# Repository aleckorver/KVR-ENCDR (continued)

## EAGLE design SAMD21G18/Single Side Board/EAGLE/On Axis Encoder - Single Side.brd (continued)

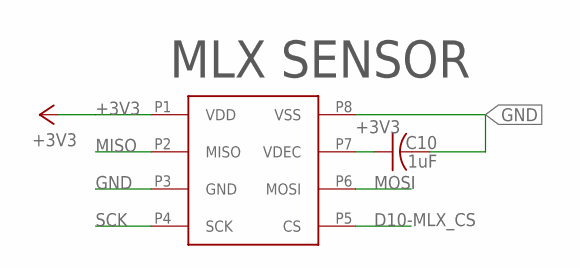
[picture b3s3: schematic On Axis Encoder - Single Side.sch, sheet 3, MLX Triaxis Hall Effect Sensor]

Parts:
C10: 1uF; C0603
U$4: MLX90363-SOIC8; SOIC-8

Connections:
+3V3: C10.1, U$4.P1 (VDD), U$4.P7 (VDEC); also elsewhere on the board
D10-MLX_CS: U$4.P5 (CS); also elsewhere on the board
GND: C10.2, U$4.P3 (GND), U$4.P8 (VSS); also elsewhere on the board
MISO: U$4.P2 (MISO); also elsewhere on the board
MOSI: U$4.P6 (MOSI); also elsewhere on the board
SCK: U$4.P4 (SCK); also elsewhere on the board

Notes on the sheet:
MLX SENSOR

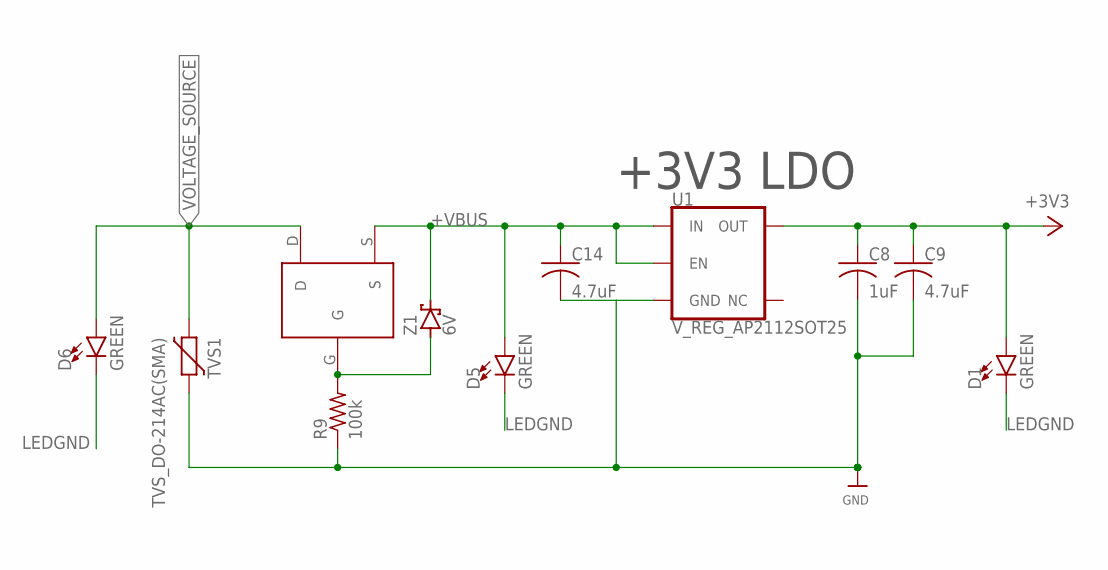
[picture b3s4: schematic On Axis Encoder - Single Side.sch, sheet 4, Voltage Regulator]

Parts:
C8: 1uF; C0603
C9, C14: 4.7uF; C0603
D1, D5, D6: GREEN; LED-0603
PFET1: PFET; SOT323-3_NFET
R9: 100k; R0603
TVS1: TVS_DO-214AC(SMA); DIOM5226X290N
U1: V_REG_AP2112SOT25; SOT95P285X140-5N
Z1: 6V; SOT23

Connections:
+3V3: C8.1, C9.1, D1.A, U1.5 (OUT); also elsewhere on the board
+VBUS: C14.1, D5.A, PFET1.S, U1.1 (IN), U1.3 (EN), Z1.3 (C); also elsewhere on the board
GND: C8.2, C9.2, C14.2, R9.1, TVS1.2, U1.2 (GND); also elsewhere on the board
LEDGND: D1.C, D5.C, D6.C; also elsewhere on the board
unnamed: PFET1.G, R9.2, Z1.1 (A)
VOLTAGE_SOURCE: D6.A, PFET1.D, TVS1.1; also elsewhere on the board

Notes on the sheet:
+3V3 LDO

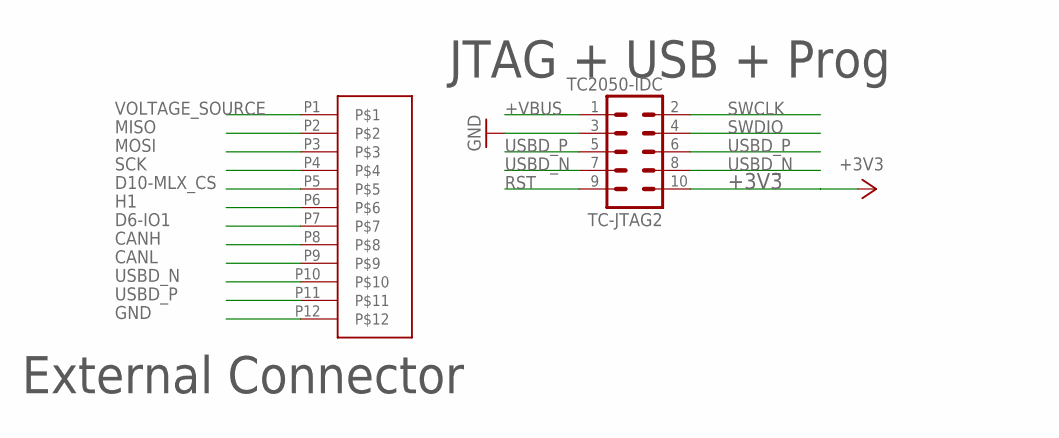
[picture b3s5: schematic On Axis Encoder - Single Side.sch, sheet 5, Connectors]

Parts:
TC-JTAG2: TC2050-IDC
U$9: BM12B-ZESS-TBT; JST-BM12B-ZESS-TBT

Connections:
+3V3: TC-JTAG2.10; also elsewhere on the board
+VBUS: TC-JTAG2.1; also elsewhere on the board
CANH: U$9.P8; also elsewhere on the board
CANL: U$9.P9; also elsewhere on the board
D6-IO1: U$9.P7; also elsewhere on the board
D10-MLX_CS: U$9.P5; also elsewhere on the board
GND: TC-JTAG2.3, U$9.P12; also elsewhere on the board
H1: U$9.P6; also elsewhere on the board
MISO: U$9.P2; also elsewhere on the board
MOSI: U$9.P3; also elsewhere on the board
RST: TC-JTAG2.9; also elsewhere on the board
SCK: U$9.P4; also elsewhere on the board
SWCLK: TC-JTAG2.2; also elsewhere on the board
SWDIO: TC-JTAG2.4; also elsewhere on the board
USBD_N: TC-JTAG2.7, TC-JTAG2.8, U$9.P10; also elsewhere on the board
USBD_P: TC-JTAG2.5, TC-JTAG2.6, U$9.P11; also elsewhere on the board
VOLTAGE_SOURCE: U$9.P1; also elsewhere on the board

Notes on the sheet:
JTAG + USB + Prog
External Connector

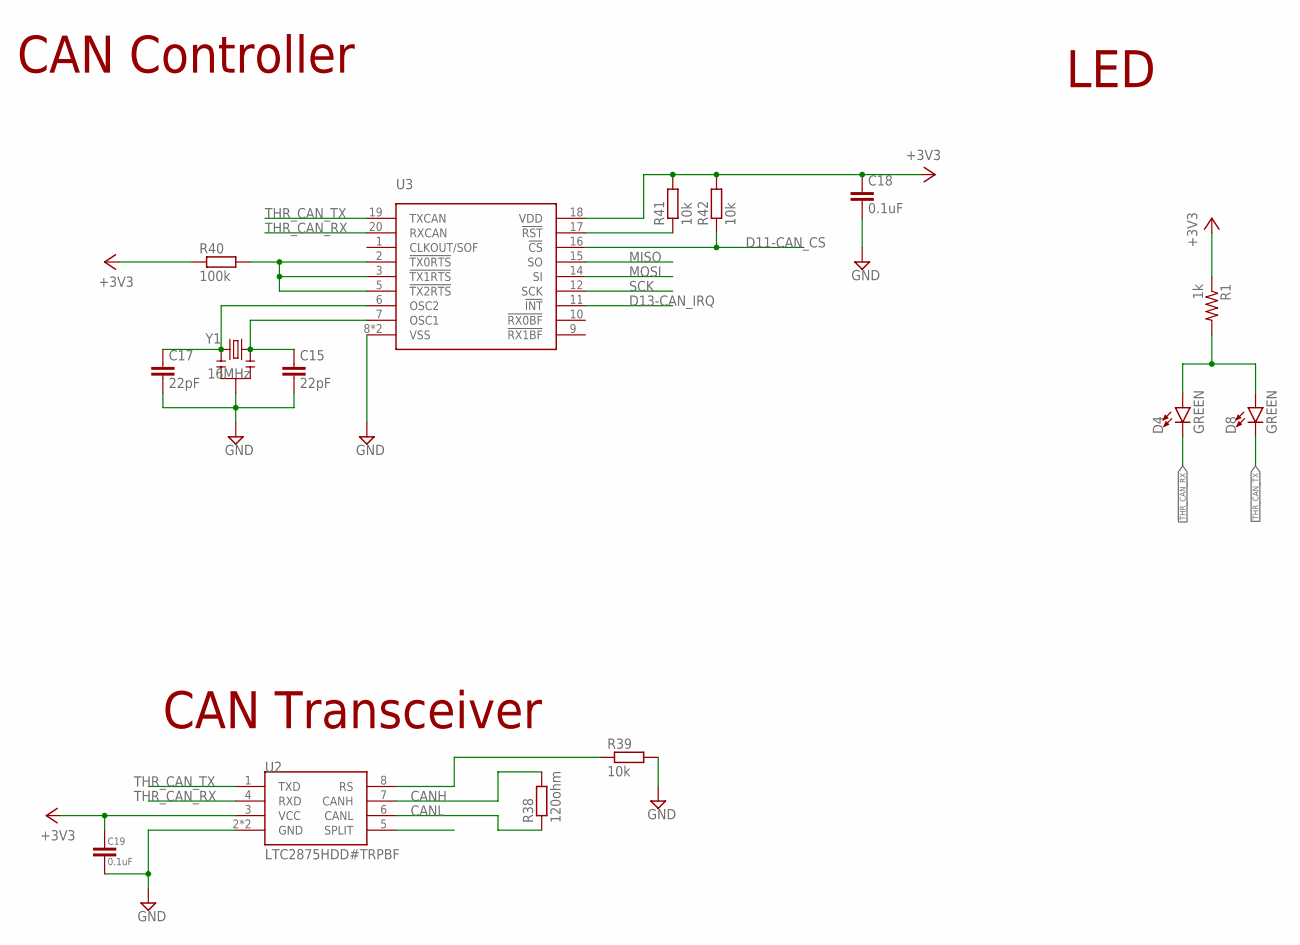
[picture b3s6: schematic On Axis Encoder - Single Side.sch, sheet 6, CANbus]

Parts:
C15, C17: 22pF; C-0603
C18, C19: 0.1uF; C-0603
D4, D8: GREEN; LED-0603
R1: 1k; R0603
R38: 120ohm; R-0603
R39, R41, R42: 10k; R-0603
R40: 100k; R-0603
U2: LTC2875HDD#TRPBF; SON50P300X300X80-9T165X238N
U3: MCP2515-E/ML; QFN50P400X400X100-21T270N
Y1: 16MHz; RESONATOR-SMD

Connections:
+3V3: C18.P$1 (1), C19.P$1 (1), R1.1, R40.P$1 (1), R41.P$2 (2), R42.P$2 (2), U2.3 (VCC), U3.18 (VDD); also elsewhere on the board
CANH: R38.P$2 (2), U2.7 (CANH); also elsewhere on the board
CANL: R38.P$1 (1), U2.6 (CANL); also elsewhere on the board
D11-CAN_CS: R42.P$1 (1), U3.16 (!CS); also elsewhere on the board
D13-CAN_IRQ: U3.11 (!INT); also elsewhere on the board
GND: C15.P$2 (2), C17.P$2 (2), C18.P$2 (2), C19.P$2 (2), R39.P$2 (2), U2.2 (GND), U2.9 (GND), U3.8 (VSS), U3.21 (VSS), Y1.2; also elsewhere on the board
MISO: U3.15 (SO); also elsewhere on the board
MOSI: U3.14 (SI); also elsewhere on the board
unnamed: D4.A, D8.A, R1.2
unnamed: R39.P$1 (1), U2.8 (RS)
unnamed: R41.P$1 (1), U3.17 (!RST)
unnamed: R40.P$2 (2), U3.2 (!TX0RTS), U3.3 (!TX1RTS), U3.5 (!TX2RTS)
unnamed: C17.P$1 (1), U3.6 (OSC2), Y1.3
unnamed: C15.P$1 (1), U3.7 (OSC1), Y1.1
SCK: U3.12 (SCK); also elsewhere on the board
THR_CAN_RX: D4.C, U2.4 (RXD), U3.20 (RXCAN)
THR_CAN_TX: D8.C, U2.1 (TXD), U3.19 (TXCAN)

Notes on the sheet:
CAN Transceiver
CAN Controller
LED

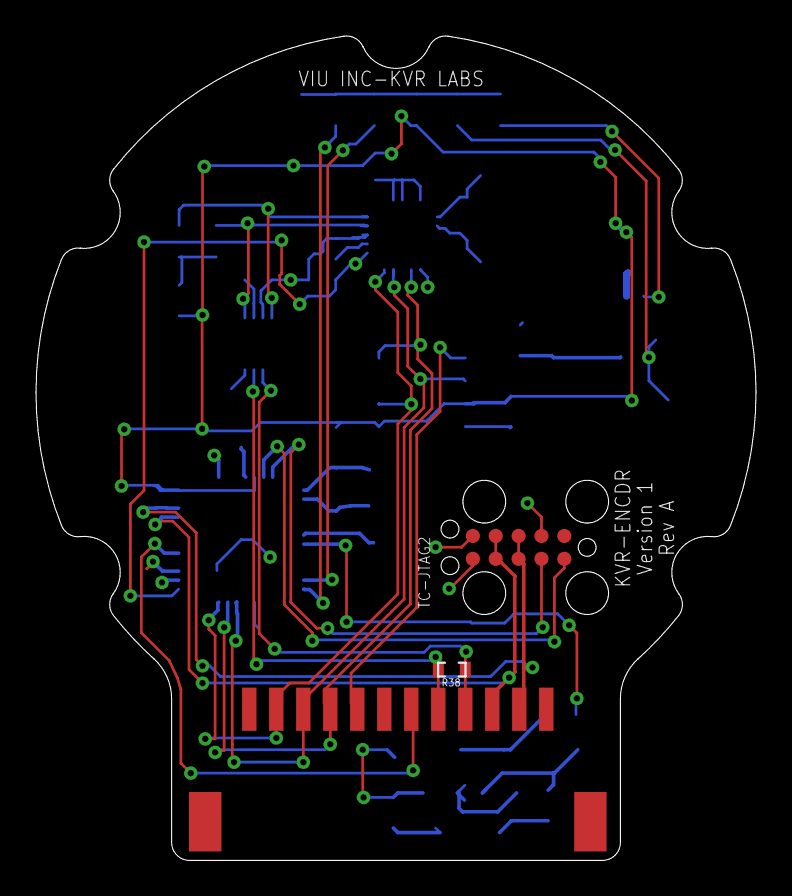
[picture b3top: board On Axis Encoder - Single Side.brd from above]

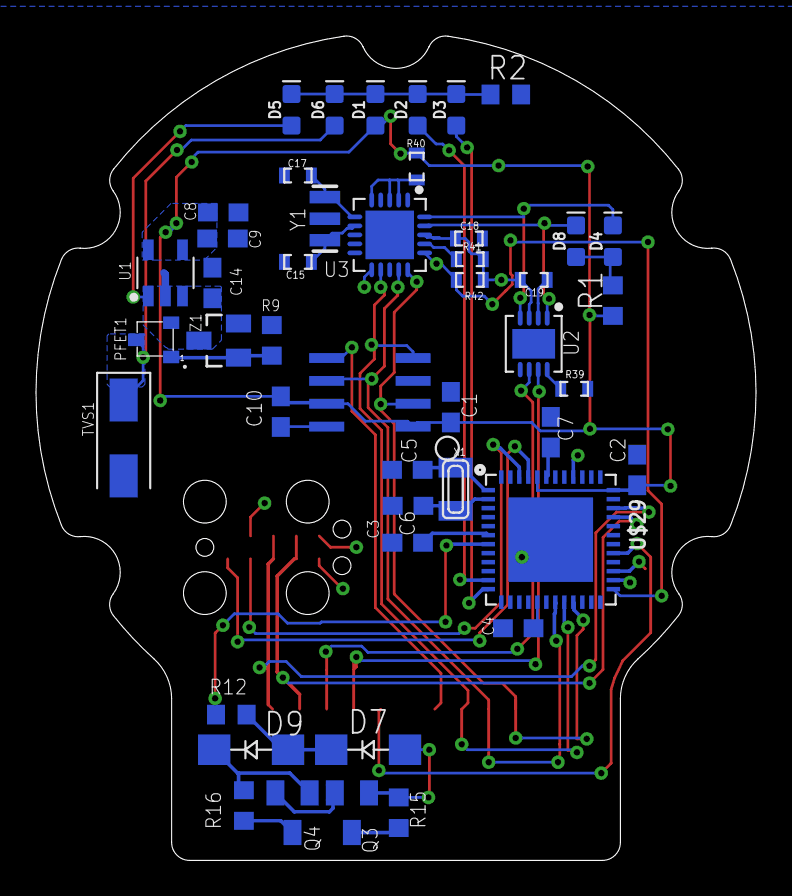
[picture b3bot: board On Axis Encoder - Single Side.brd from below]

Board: 4 copper layers, 40.0 x 45.8 mm, 49 parts (46 on the bottom side), 39 nets.

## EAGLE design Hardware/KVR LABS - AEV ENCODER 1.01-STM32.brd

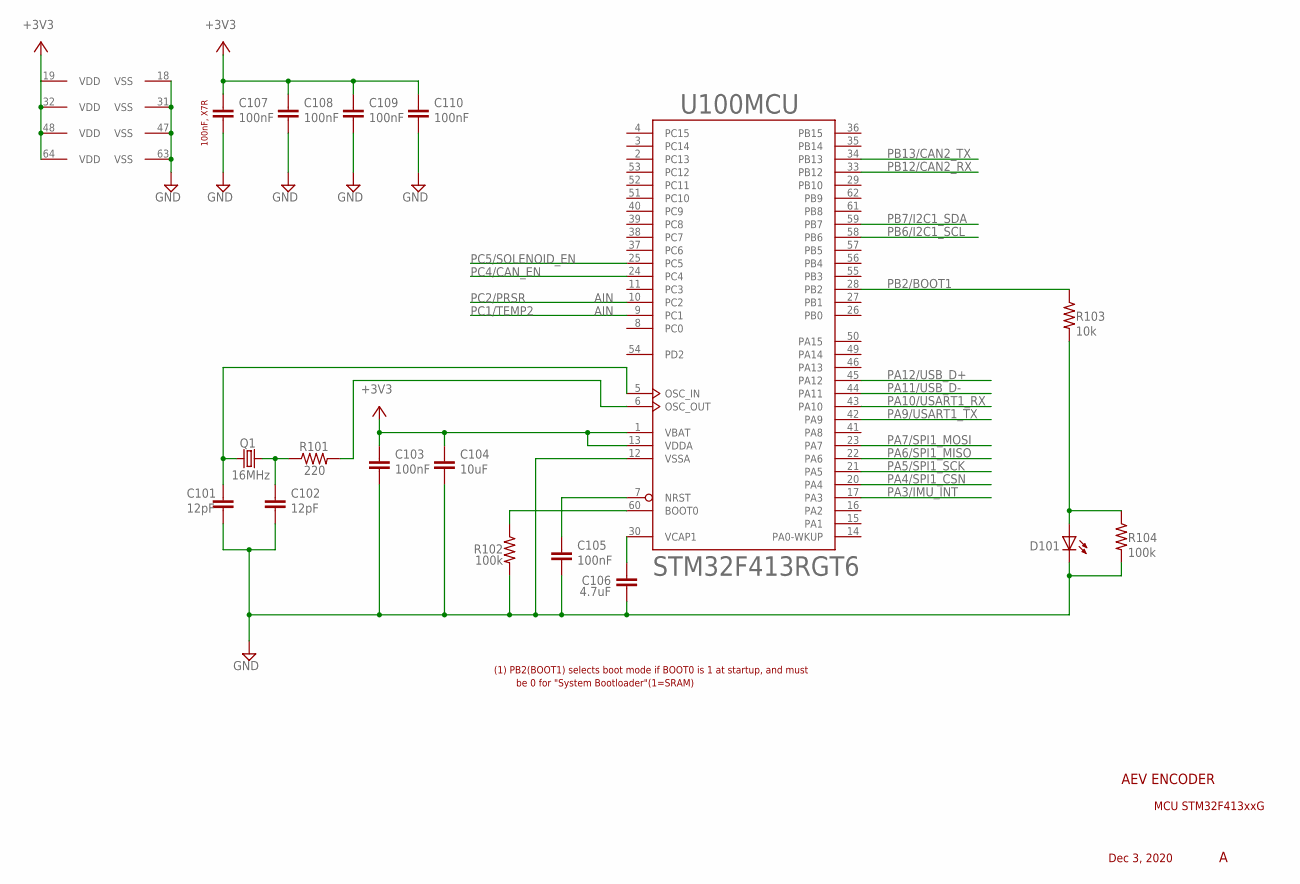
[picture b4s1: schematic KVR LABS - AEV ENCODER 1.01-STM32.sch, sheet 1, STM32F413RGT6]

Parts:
C101, C102: 12pF; C0603
C103, C105, C107, C108, C109, C110: 100nF; C0603
C104: 10uF; C0603
C106: 4.7uF; C0603
D101: LEDCHIPLED_0805; CHIPLED_0805
Q1: 16MHz; CRY3225-4
R101: 220; R0603
R102, R104: 100k; R0603
R103: 10k; R0603
U100: STM32F413RGT6; LQFP64_STMLIB

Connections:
+3V3: C103.1, C104.1, C107.1, C108.1, C109.1, C110.1, U100.1 (VBAT), U100.13 (VDDA), U100.19 (VDD), U100.32 (VDD), U100.48 (VDD), U100.64 (VDD); also elsewhere on the board
BOOT0: R102.1, U100.60 (BOOT0); also elsewhere on the board
GND: C101.2, C102.2, C103.2, C104.2, C105.2, C106.2, C107.2, C108.2, C109.2, C110.2, D101.C, R102.2, R104.2, U100.12 (VSSA), U100.18 (VSS), U100.31 (VSS), U100.47 (VSS), U100.63 (VSS); also elsewhere on the board
unnamed: D101.A, R103.2, R104.1
unnamed: R101.2, U100.6 (OSC_OUT)
NRST: C105.1, U100.7 (NRST)
OSC_IN: C101.1, Q1.3 (2), U100.5 (OSC_IN)
OSC_OUT: C102.1, Q1.1, R101.1
PA3/IMU_INT: U100.17 (PA3); also elsewhere on the board
PA4/SPI1_CSN: U100.20 (PA4); also elsewhere on the board
PA5/SPI1_SCK: U100.21 (PA5); also elsewhere on the board
PA6/SPI1_MISO: U100.22 (PA6); also elsewhere on the board
PA7/SPI1_MOSI: U100.23 (PA7); also elsewhere on the board
PA9/USART1_TX: U100.42 (PA9); also elsewhere on the board
PA10/USART1_RX: U100.43 (PA10); also elsewhere on the board
PA11/USB_D-: U100.44 (PA11); also elsewhere on the board
PA12/USB_D+: U100.45 (PA12); also elsewhere on the board
PB2/BOOT1: R103.1, U100.28 (PB2); also elsewhere on the board
PB6/I2C1_SCL: U100.58 (PB6); also elsewhere on the board
PB7/I2C1_SDA: U100.59 (PB7); also elsewhere on the board
PB12/CAN2_RX: U100.33 (PB12); also elsewhere on the board
PB13/CAN2_TX: U100.34 (PB13); also elsewhere on the board
PC1/TEMP2: U100.9 (PC1); also elsewhere on the board
PC2/PRSR: U100.10 (PC2); also elsewhere on the board
PC4/CAN_EN: U100.24 (PC4); also elsewhere on the board
PC5/SOLENOID_EN: U100.25 (PC5); also elsewhere on the board
VCAP: C106.1, U100.30 (VCAP1)

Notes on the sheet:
AEV ENCODER
MCU STM32F413xxG
Dec 3, 2020
100nF, X7R
(1) PB2(BOOT1) selects boot mode if BOOT0 is 1 at startup, and must
be 0 for "System Bootloader"(1=SRAM)
AIN

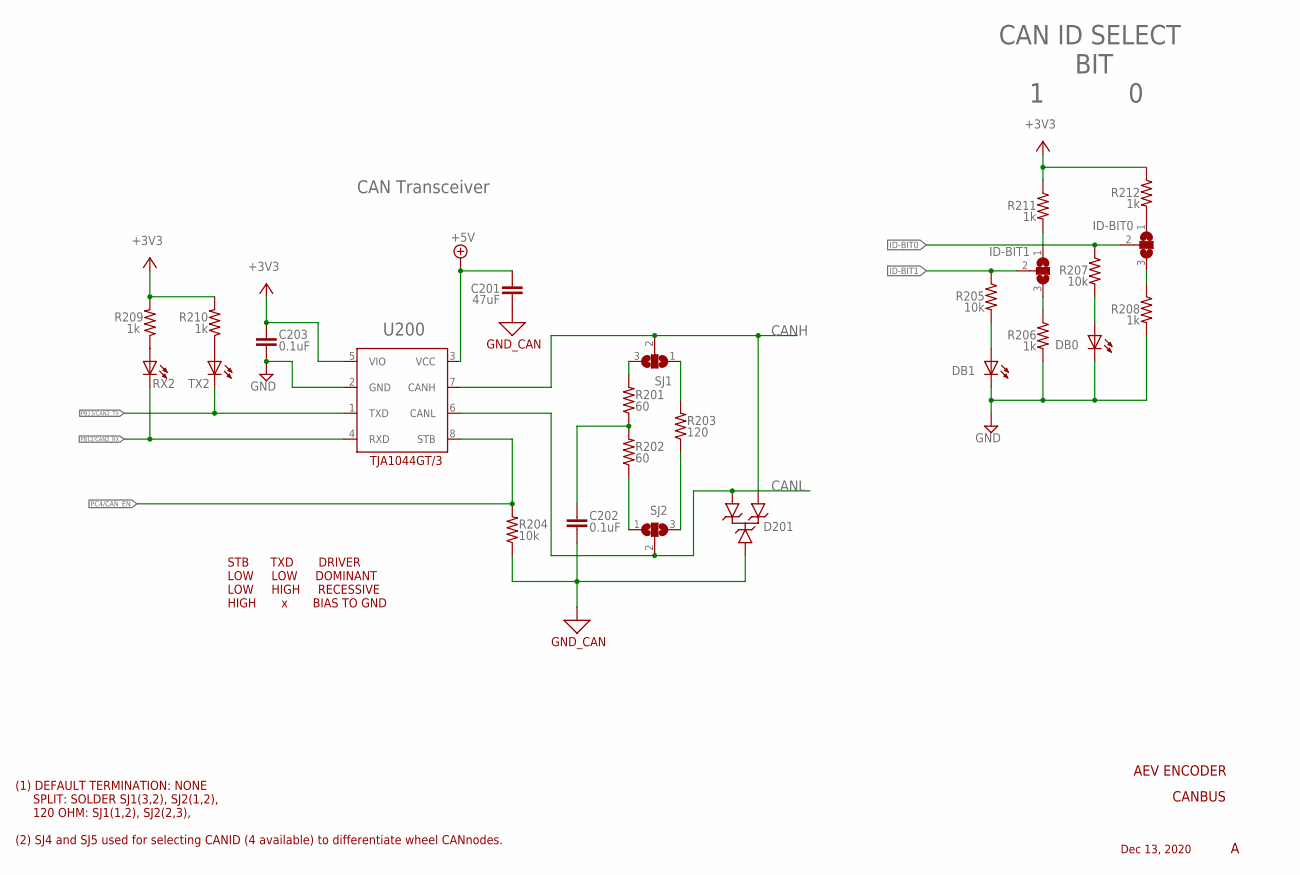
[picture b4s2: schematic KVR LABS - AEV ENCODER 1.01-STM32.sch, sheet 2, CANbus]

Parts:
C201: 47uF; C0603
C202, C203: 0.1uF; C0603
D201: μCLAMP2492SQ; SOT-23_3L_ONS
DB0, DB1: LEDCHIPLED_0805; CHIPLED_0805
ID-BIT0, ID-BIT1: SJ2W; SJ_2
R201, R202: 60; R0603
R203: 120; R0603
R204, R205, R207: 10k; R0603
R206, R208, R209, R210, R211, R212: 1k; R0603
RX2: LEDCHIPLED_0805; CHIPLED_0805
SJ1, SJ2: SJ2W; SJ_2
TX2: LEDCHIPLED_0805; CHIPLED_0805
U200: TJA1044GT/3; SO-8_S_LIT

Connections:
+3V3: C203.1, R209.2, R210.2, R211.1, R212.1, U200.5 (VIO); also elsewhere on the board
+5V: C201.1, U200.3 (VCC); also elsewhere on the board
CANH: D201.2, SJ1.2, U200.7 (CANH); also elsewhere on the board
CANL: D201.1, SJ2.2, U200.6 (CANL); also elsewhere on the board
GND: C203.2, DB0.C, DB1.C, R206.2, R208.2, U200.2 (GND); also elsewhere on the board
GND_CAN: C201.2, C202.2, D201.3, R204.1; also elsewhere on the board
ID-BIT0: ID-BIT0.2, R207.1
ID-BIT1: ID-BIT1.2, R205.1
unnamed: ID-BIT1.3, R206.1
unnamed: ID-BIT0.3, R208.1
unnamed: DB0.A, R207.2
unnamed: DB1.A, R205.2
unnamed: ID-BIT1.1, R211.2
unnamed: ID-BIT0.1, R212.2
unnamed: R209.1, RX2.A
unnamed: R210.1, TX2.A
PB12/CAN2_RX: RX2.C, U200.4 (RXD); also elsewhere on the board
PB13/CAN2_TX: TX2.C, U200.1 (TXD); also elsewhere on the board
PC4/CAN_EN: R204.2, U200.8 (STB); also elsewhere on the board
RSH: R201.2, SJ1.3
RSL: R202.1, SJ2.1
RTH: R203.2, SJ1.1
RTL: R203.1, SJ2.3
SPLIT: C202.1, R201.1, R202.2

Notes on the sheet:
CANBUS
AEV ENCODER
Dec 13, 2020
(1) DEFAULT TERMINATION: NONE SPLIT: SOLDER SJ1(3,2), SJ2(1,2), 120 OHM: SJ1(1,2), SJ2(2,3), (2) SJ4 and SJ5 used for selecting CANID (4 available) to differentiate wheel CANnodes.
CAN ID SELECT BIT 1 0
D201
CAN Transceiver
U200
STB TXD DRIVER LOW LOW DOMINANT LOW HIGH RECESSIVE HIGH x BIAS TO GND

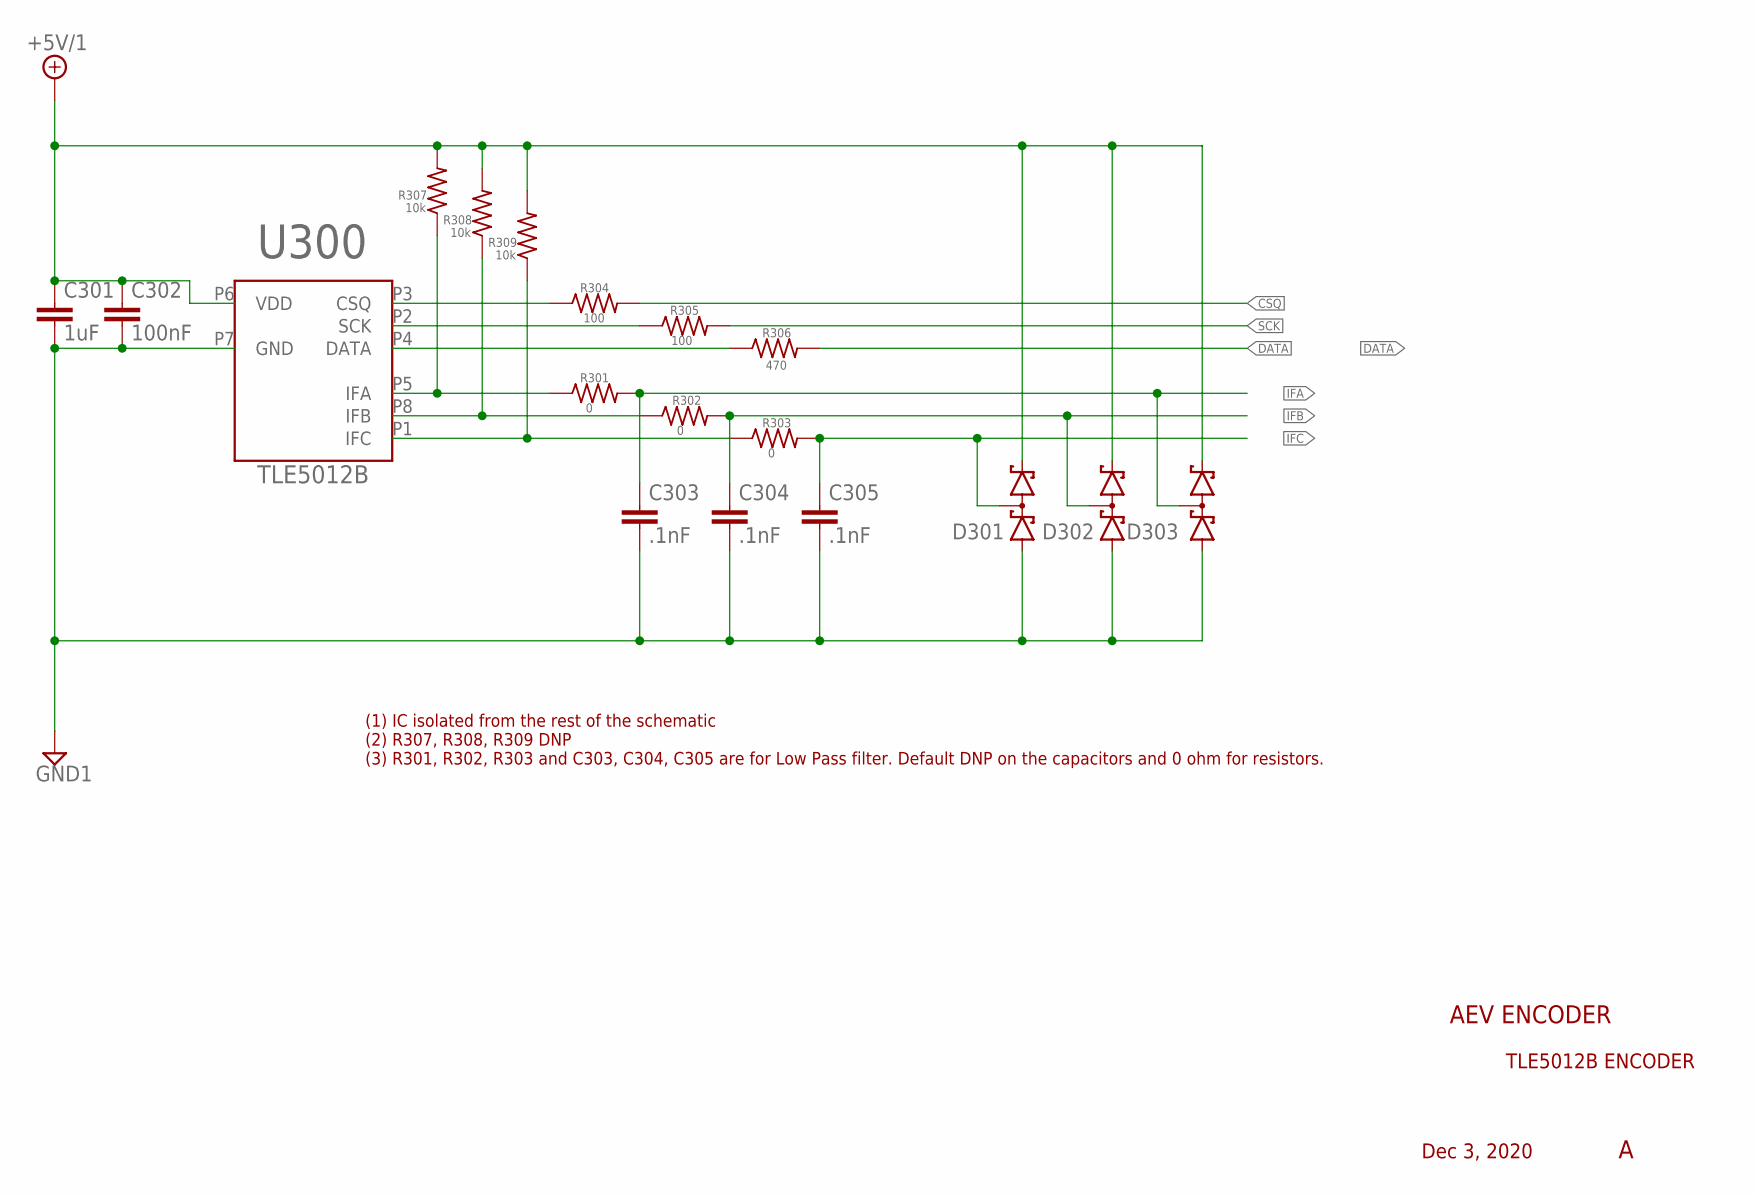
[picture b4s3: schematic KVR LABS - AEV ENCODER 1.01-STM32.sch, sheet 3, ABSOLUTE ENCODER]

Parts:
C301: 1uF; C0603
C302: 100nF; C0603
C303, C304, C305: .1nF; C0603
D301, D302, D303: BAS70-04; SOT23
R301, R302, R303: 0; R0603
R304, R305: 100; R0603
R306: 470; R0603
R307, R308, R309: 10k; R0603
U300: TLE5012B; PG-DSO-8

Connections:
+5V/1: C301.1, C302.1, D301.2 (C2), D302.2 (C2), D303.2 (C2), R307.2, R308.2, R309.2, U300.P6 (VDD); also elsewhere on the board
CSQ: R304.2; also elsewhere on the board
DATA: R306.2; also elsewhere on the board
GND1: C301.2, C302.2, C303.2, C304.2, C305.2, D301.1 (A1), D302.1 (A1), D303.1 (A1), U300.P7 (GND); also elsewhere on the board
IFA: C303.1, D303.3 (C1A2), R301.2; also elsewhere on the board
IFB: C304.1, D302.3 (C1A2), R302.2; also elsewhere on the board
IFC: C305.1, D301.3 (C1A2), R303.2; also elsewhere on the board
unnamed: R304.1, U300.P3 (CSQ)
unnamed: R305.1, U300.P2 (SCK)
unnamed: R306.1, U300.P4 (DATA)
unnamed: R301.1, R307.1, U300.P5 (IFA)
unnamed: R302.1, R308.1, U300.P8 (IFB)
unnamed: R303.1, R309.1, U300.P1 (IFC)
SCK: R305.2; also elsewhere on the board

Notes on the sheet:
TLE5012B
AEV ENCODER
TLE5012B ENCODER
Dec 3, 2020
U300
(1) IC isolated from the rest of the schematic (2) R307, R308, R309 DNP (3) R301, R302, R303 and C303, C304, C305 are for Low Pass filter. Default DNP on the capacitors and 0 ohm for resistors.

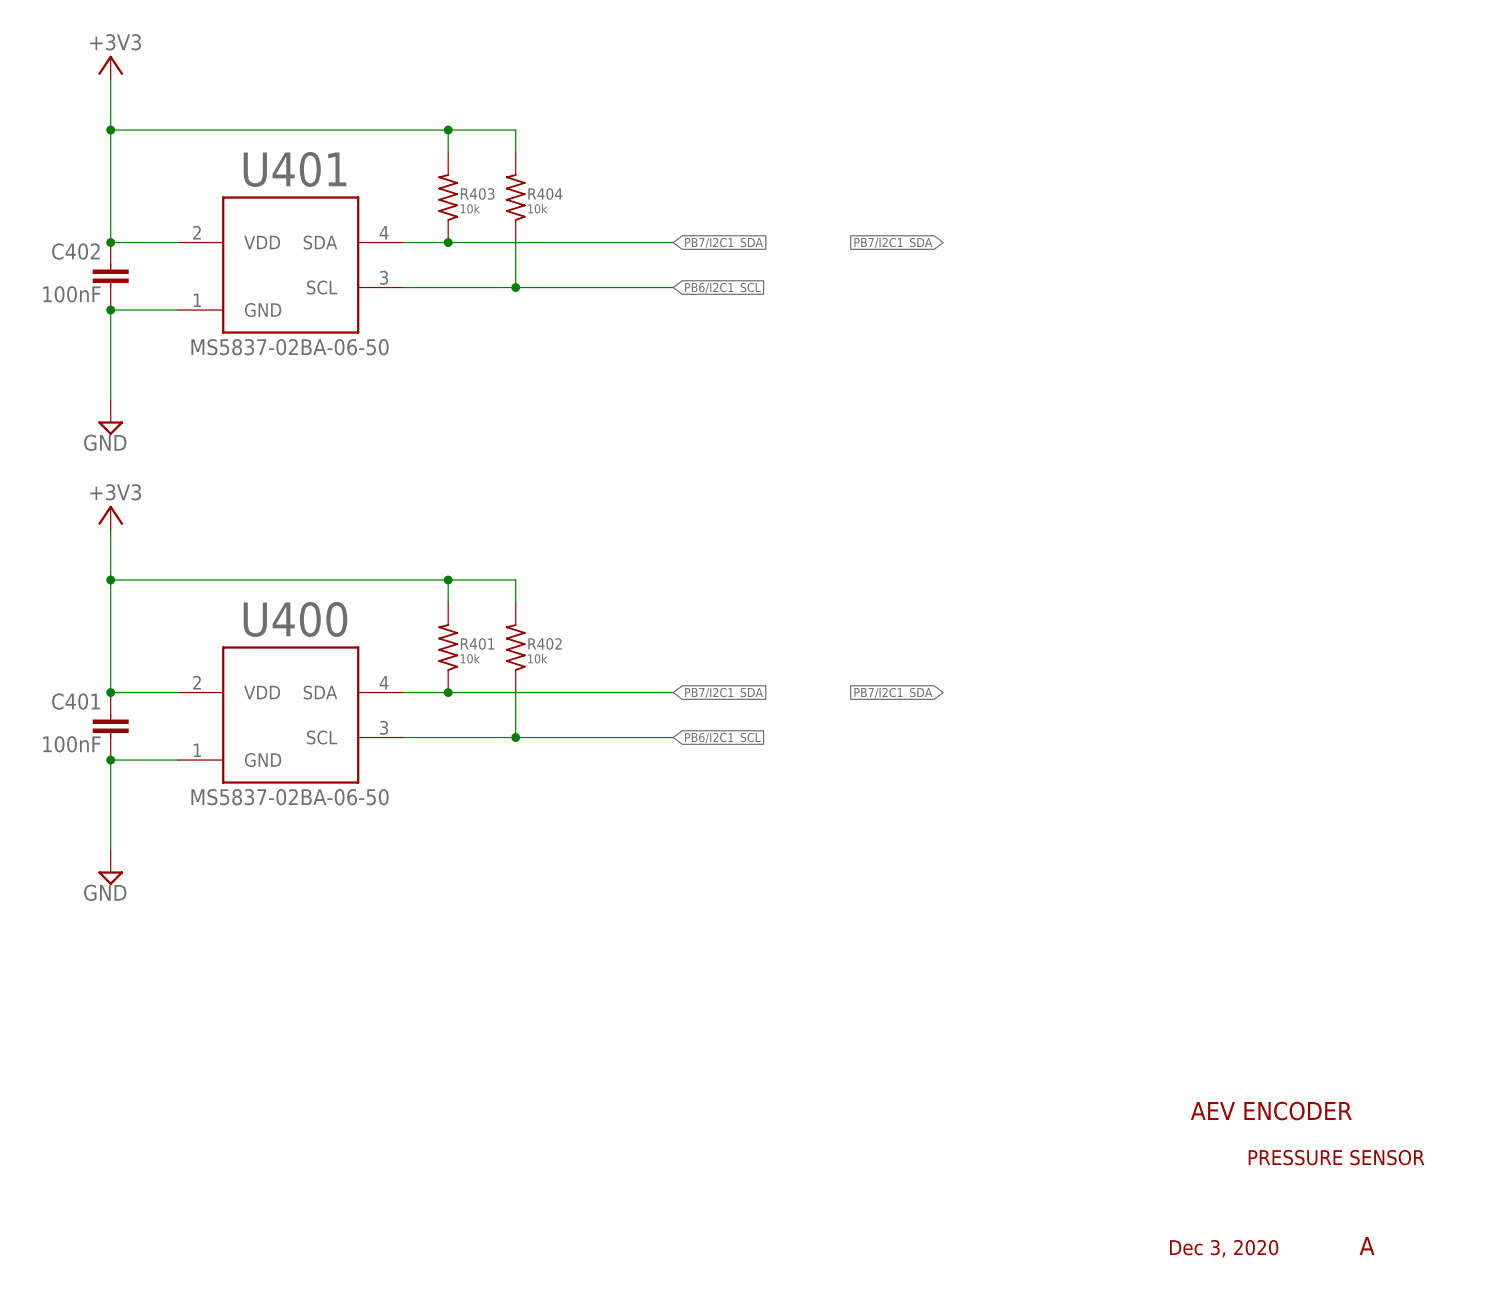
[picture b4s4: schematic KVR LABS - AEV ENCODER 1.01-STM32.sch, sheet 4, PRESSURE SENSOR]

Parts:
C401, C402: 100nF; C0603
R401, R402, R403, R404: 10k; R0603
U400, U401: MS5837-02BA-06-50; DFN330X330X275-4N

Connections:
+3V3: C401.1, C402.1, R401.2, R402.2, R403.2, R404.2, U400.2 (VDD), U401.2 (VDD); also elsewhere on the board
GND: C401.2, C402.2, U400.1 (GND), U401.1 (GND); also elsewhere on the board
PB6/I2C1_SCL: R402.1, R404.1, U400.3 (SCL), U401.3 (SCL); also elsewhere on the board
PB7/I2C1_SDA: R401.1, R403.1, U400.4 (SDA), U401.4 (SDA); also elsewhere on the board

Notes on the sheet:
AEV ENCODER
PRESSURE SENSOR
Dec 3, 2020

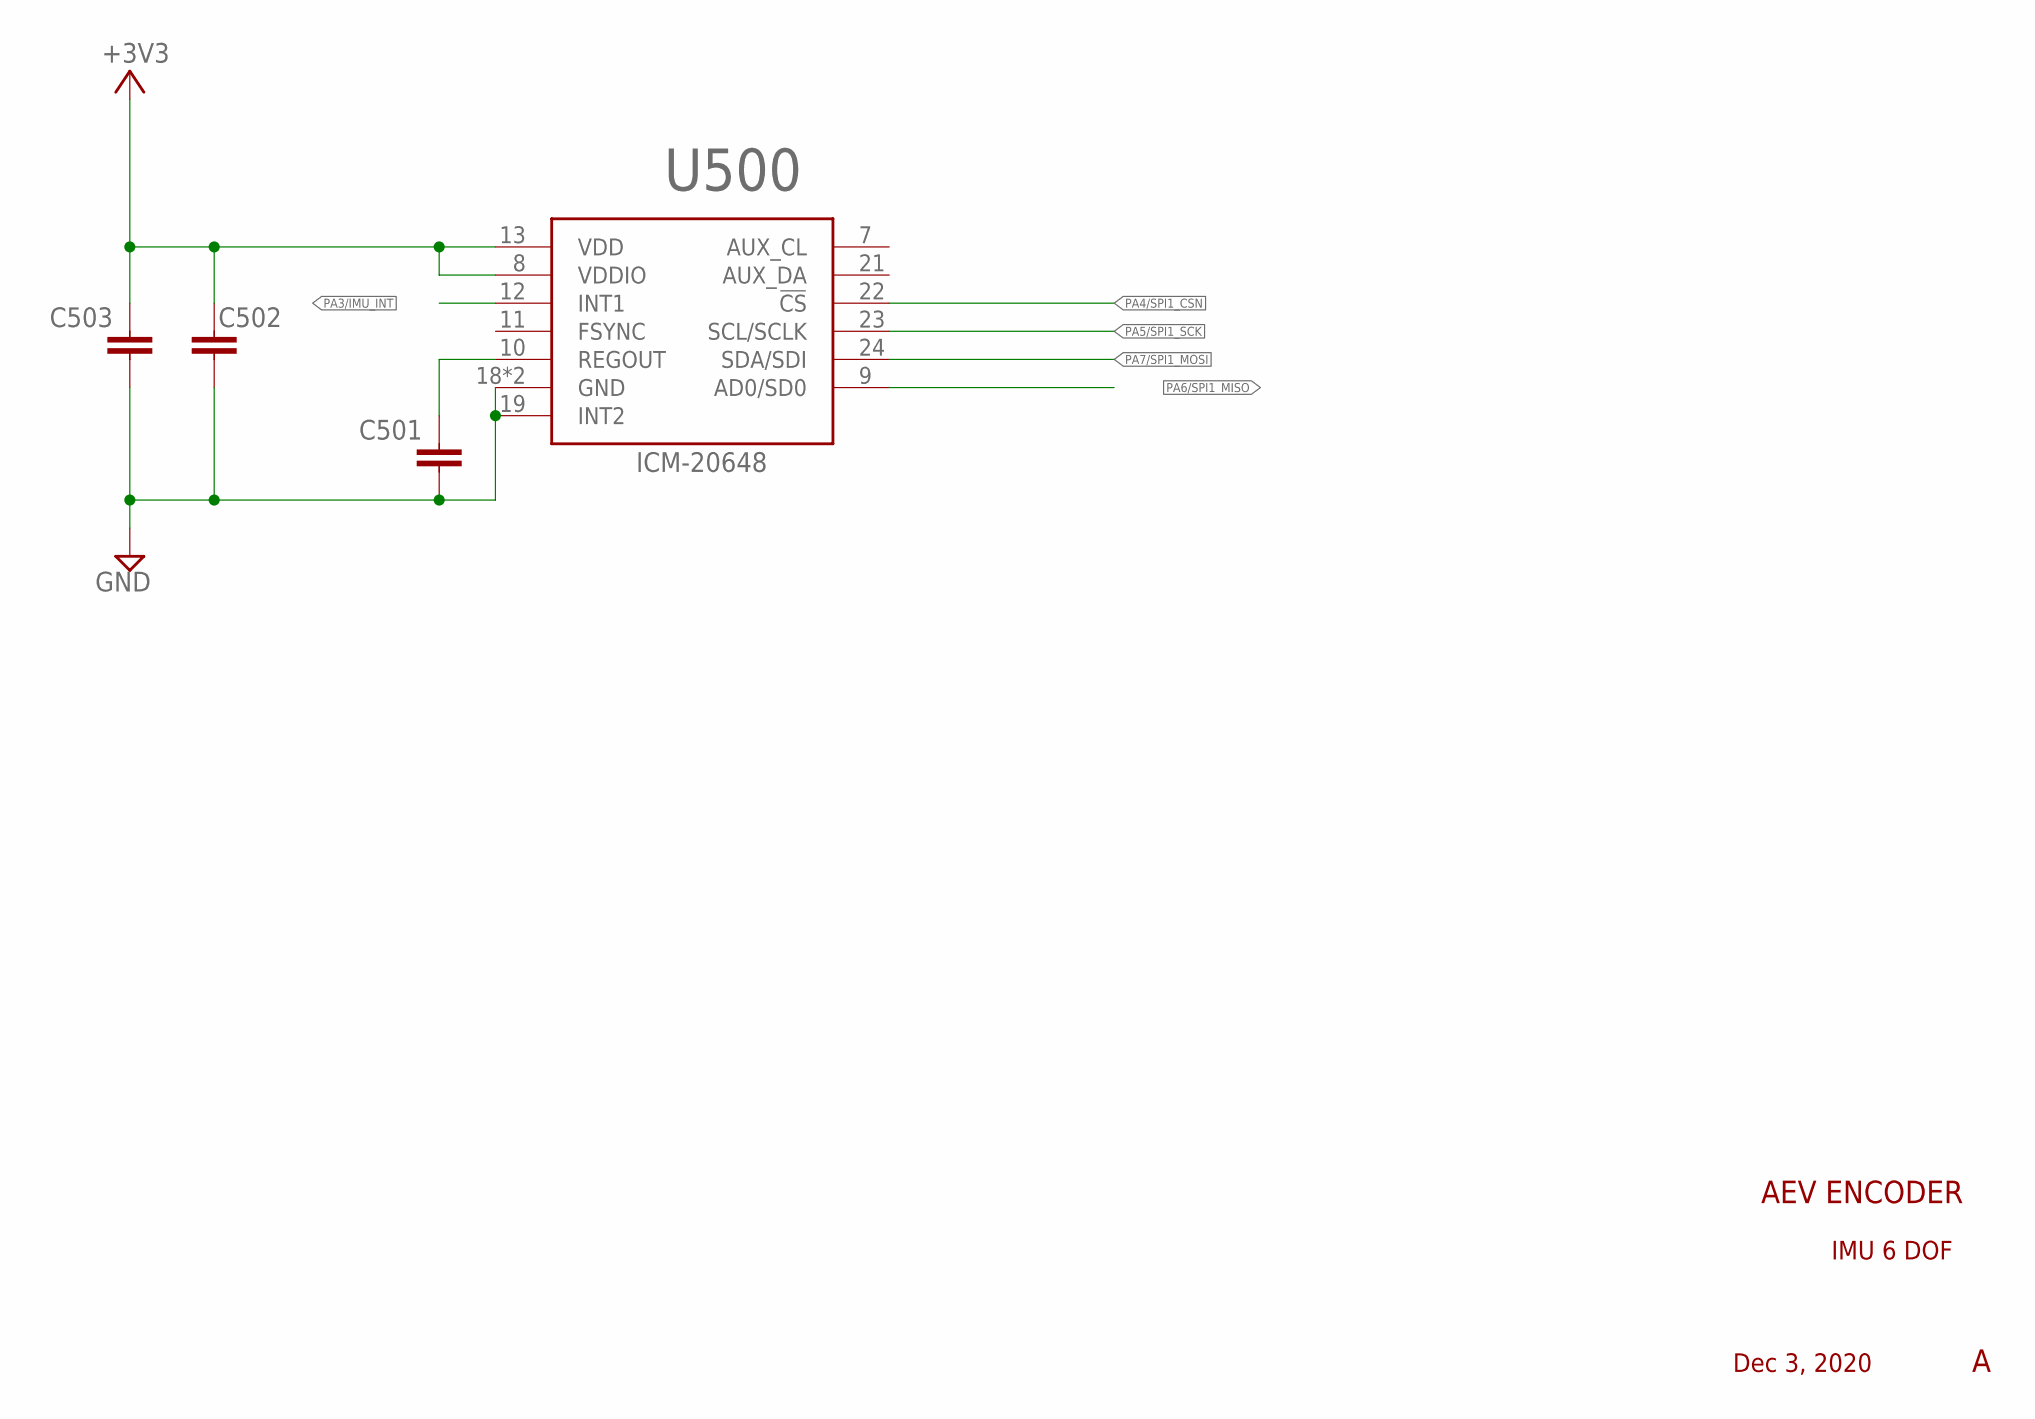
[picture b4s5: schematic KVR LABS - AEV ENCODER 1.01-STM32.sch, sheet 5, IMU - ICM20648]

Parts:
C501, C502, C503: 0.1uF; C0603
U500: ICM-20648

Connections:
+3V3: C502.1, C503.1, U500.8 (VDDIO), U500.13 (VDD); also elsewhere on the board
GND: C501.2, C502.2, C503.2, U500.18 (GND), U500.19 (INT2), U500.20 (GND); also elsewhere on the board
PA3/IMU_INT: U500.12 (INT1); also elsewhere on the board
PA4/SPI1_CSN: U500.22 (!CS); also elsewhere on the board
PA5/SPI1_SCK: U500.23 (SCL/SCLK); also elsewhere on the board
PA6/SPI1_MISO: U500.9 (AD0/SD0); also elsewhere on the board
PA7/SPI1_MOSI: U500.24 (SDA/SDI); also elsewhere on the board
REGOUT2: C501.1, U500.10 (REGOUT)

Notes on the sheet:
AEV ENCODER
IMU 6 DOF
Dec 3, 2020

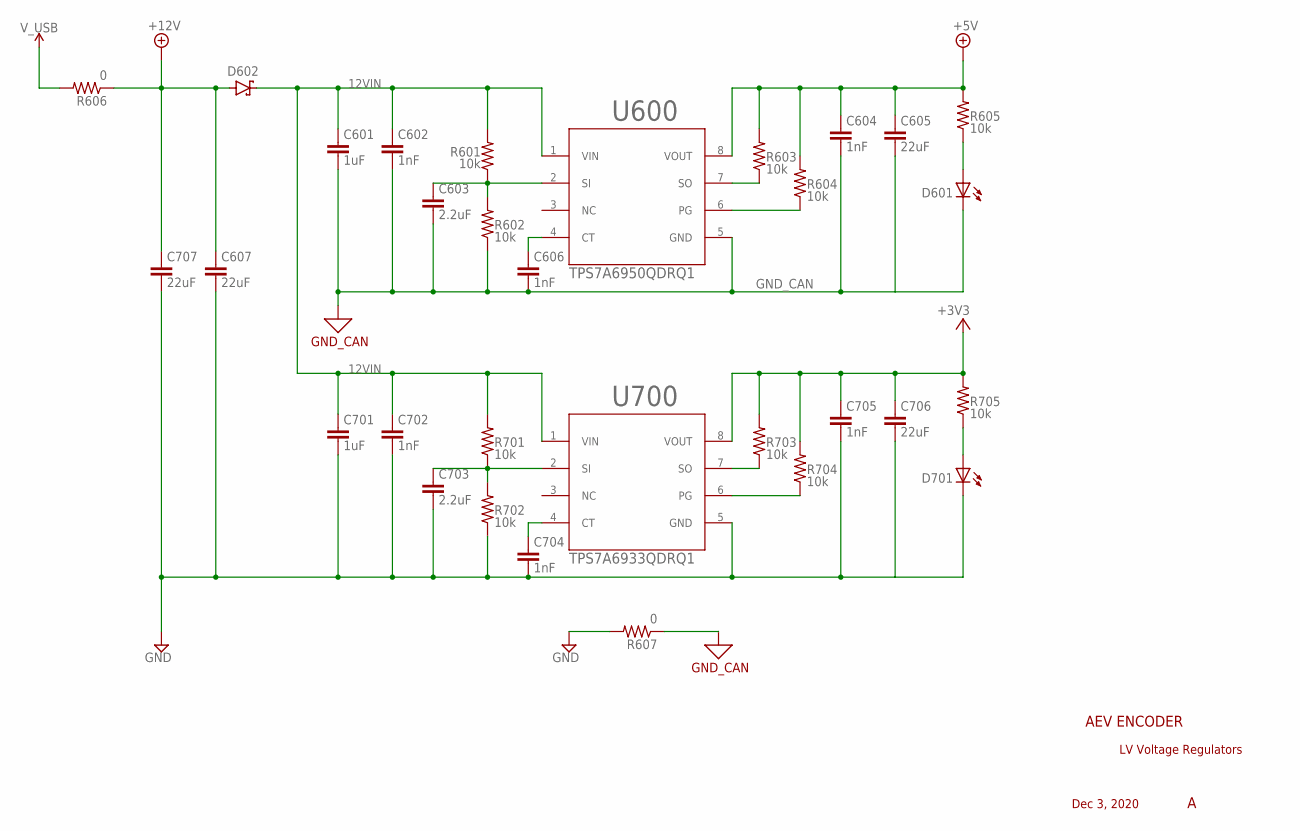
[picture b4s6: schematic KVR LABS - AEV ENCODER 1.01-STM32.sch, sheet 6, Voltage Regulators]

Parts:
C601, C701: 1uF; C0603
C602, C604, C606, C702, C704, C705: 1nF; C0603
C603, C703: 2.2uF; C0603
C605, C706: 22uF; C0603
C607, C707: 22uF; C1206
D601, D701: LEDCHIPLED_0805; CHIPLED_0805
D602: MBR0520LT1G; SODFL3718X115
R601, R602, R603, R604, R605, R701, R702, R703, R704, R705: 10k; R0603
R606, R607: 0; R0805
U600, U700: Value; D0008A_N

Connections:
12VIN: C601.1, C602.1, C701.1, C702.1, D602.1 (C), R601.2, R701.2, U600.1 (VIN), U700.1 (VIN)
+3V3: C705.1, C706.1, R703.2, R704.2, R705.2, U700.8 (VOUT); also elsewhere on the board
+5V: C604.1, C605.1, R603.2, R604.2, R605.2, U600.8 (VOUT); also elsewhere on the board
+12V: C607.1, C707.1, D602.2 (A), R606.1; also elsewhere on the board
GND: C607.2, C701.2, C702.2, C703.2, C704.2, C705.2, C706.2, C707.2, D701.C, R607.2, R702.1, U700.5 (GND); also elsewhere on the board
GND_CAN: C601.2, C602.2, C603.2, C604.2, C605.2, C606.2, D601.C, R602.1, R607.1, U600.5 (GND); also elsewhere on the board
unnamed: D701.A, R705.1
unnamed: C603.1, R601.1, R602.2, U600.2 (SI)
unnamed: C703.1, R701.1, R702.2, U700.2 (SI)
unnamed: R704.1, U700.6 (PG)
unnamed: R703.1, U700.7 (SO)
unnamed: C704.1, U700.4 (CT)
unnamed: R604.1, U600.6 (PG)
unnamed: R603.1, U600.7 (SO)
unnamed: C606.1, U600.4 (CT)
unnamed: D601.A, R605.1
V_USB: R606.2; also elsewhere on the board

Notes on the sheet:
TPS7A6933QDRQ1
TPS7A6950QDRQ1
AEV ENCODER
LV Voltage Regulators
Dec 3, 2020
